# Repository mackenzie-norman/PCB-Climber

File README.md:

# PCB Climber 
Mackenzie Norman

This started as my attempt to implement the GA described in this [paper](https://asmedigitalcollection.asme.org/electronicpackaging/article-abstract/118/1/11/404553/PCB-Layout-Design-Using-a-Genetic-Algorithm?redirectedFrom=fulltext) using the Rust Programming language 

Note: since it is paywalled, and to make sure I knew what I was doing. I rewrote the key pieces here : [GA_breakdown.pdf](GA_breakdown.pdf)

This project uses a Genetic Algorithm (GA) to generate "good" pcb layouts. It can read in some .kicad_pcb files. It features a CLI using CLAP and is multithreaded using Rayon. It also uses the plotters library to make nice plots of  placements.

The GA optimizes for 3 variables which are summed to calculate the fitness. 
- HPWL: calculated on a per net basis. In the real world, layouts with Via anywhere don't need to worry about routing gnd so I sometimes ignore it.
- placement area: currently this is just the bounding box of all the components, ideally this should be Convex Hull or some other more accurate area calculation
- Overlap: A large penalty is added if components overlap.

# Building 
to build the exe simply run :
```cargo build --release``` 
the .exe will then be in 
`target\release\pcb-layout.exe`

# Usage 
Now either with the path above, or just with `cargo run --release --` you can run the exe and use the cli. 
```
Usage: pcb-layout.exe [OPTIONS]

Options:
  -f, --file <FILE>
          Name of the .kicad_pcb file to use. Use synthetic to use the generated toy case. This probably will error on some boards. The parser was a bit of an afterthought and desperately needs more time [default: "../arduino_kicad/arduino UNO.kicad_pcb"]
  -g, --generations <GENERATIONS>
          Number of generations [default: 1000]
  -p, --population-size <POPULATION_SIZE>
          How many individuals are in our popuation [default: 100]
  -t, --test
          Run the testing function on our file (will override gen/pop)- right now this is the only way to see SA results too
  -s, --selection
          Selection Type (ev or elitist) 
  -a, --animate
          Generate an animation
      --threads <THREADS>
          Number of threads (GA only), this is a bit of misnomer since its really how many groups the populations will be split into and then rayon deals with it [default: 1]
  -h, --help
          Print help
  -V, --version
          Print version
``` 

# Project Structure 

- [plcmnt.rs](pcb-layout/src/plcmnt.rs)
- [ga.rs](pcb-layout/src/ga.rs)
- [sa.rs](pcb-layout/src/sa.rs)
- [kicad_parse.rs](pcb-layout/src/kicad_parse.rs)
- [main.rs](pcb-layout/src/main.rs)

Main is our runner and cli, plus a helper function for generating a dummy placment if you don't have a kicad_pcb 
GA has our various selection operators and has the struct and impl for our individual. 
Kicad parse is for parsing kicad_pcb files. Its really ugly right now and kind of buggy I think. 
plcmnt has our struct representation of a pcb (basically, it really is just boxes and pins)

I attempted to keep an engineering notebook in [little-notebook.md](little-notebook.md).

Now that I have plotting working, you can see the progress by looking at test-100x1000.png and [test.md](pcb-layout/test.md)

# Project Write-up
## How I feel
I think this project exactly met my expectations. I still wish I could've done more. 

The hard part about stuff like this is juggling between learning and results, and I think as usual I prioritized "results" over learning and kind of wish it would've been different. 10 week terms are hard. A good example is parallelism and the rand functions. I never really got any speed ups from running things in parallel either with threads or Rayon. I assume part of this is me using clone to heavily since I did not want to deal with references and part of this is my rand function. (also maybe this isnt a great parallel problem). 

## Wins
- Did implement all my GA functionality
- Implemented an SA too and even started on a PSA. 
- Can parse a pcb (sort of)
- At least added parallel computing (using both rayon and std::threads)

## Not Wins
- Ended up giving up on the discretized version of the code - I might return to this later since I still want to do it. The main reason why this was neccessary is that most pcbs don't use whole numbers and so you'd have to scale things up and round. 
- As mentioned above, parallel did not result in meaningful run time improvement
- Using a lot of clones still. Not too expensive but there certainly can be some improvements.
- It seems like I broke it in one of the newer versions. It still runs but we get some overlaps which ideally would be filtered out
- Ran out of time to do any serious testing

## Continuations
I do plan on keeping up with this project, if nothing else to improve my rust skills. This is what I hope to change/add (in no particular order)
- finish PSA , I really think this is the best hill climber ND approach to this problem.
- Try a more 'annealing' based approach to SA. i.e instead of using purely random movement, weighting our movement and swap ops so that when temperature decreases - odds of big movements/ swaps decrease. 
- Try to get a more accurate wirelength calc - this might be something that parallel can help with.  
- Maybe try a marco or some sort of expression parser for dealing with kicad files. (I really wish the kicad parse crate had worked. )
- output back to the kicad_file

## PCB Sources:
[https://github.com/sabogalc/KiCad-Arduino-Boards](https://github.com/sabogalc/KiCad-Arduino-Boards)
## Previous Work/Sources

- [https://docs.rs/kicad_parse_gen/latest/kicad_parse_gen/layout/index.html](https://docs.rs/kicad_parse_gen/latest/kicad_parse_gen/layout/index.html)
- [https://github.com/racklet/kicad-rs/tree/main](https://github.com/racklet/kicad-rs/tree/main)
- [https://github.com/The-OpenROAD-Project/SA-PCB](https://github.com/The-OpenROAD-Project/SA-PCB)
- [https://dspace.mit.edu/bitstream/handle/1721.1/139247/Crocker-pcrocker-meng-eecs-2021-thesis.pdf?sequence=1&isAllowed=y ](https://dspace.mit.edu/bitstream/handle/1721.1/139247/Crocker-pcrocker-meng-eecs-2021-thesis.pdf?sequence=1&isAllowed=y)
- [https://ieeexplore.ieee.org/stamp/stamp.jsp?tp=&arnumber=6269973](https://ieeexplore.ieee.org/stamp/stamp.jsp?tp=&arnumber=6269973)

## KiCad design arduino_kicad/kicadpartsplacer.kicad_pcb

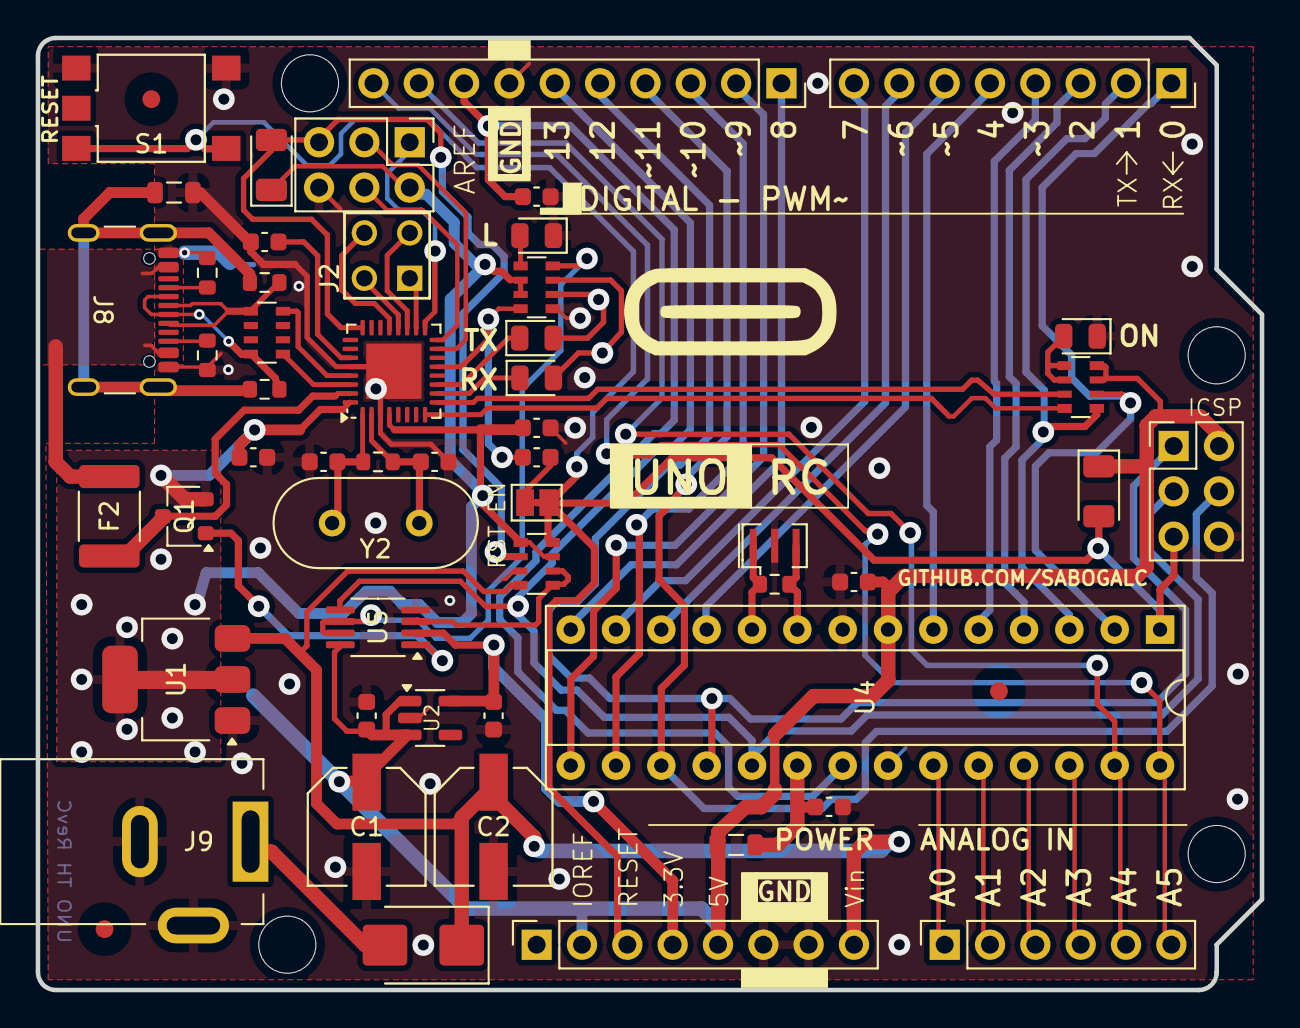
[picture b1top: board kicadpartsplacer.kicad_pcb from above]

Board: 2 copper layers, 68.6 x 53.3 mm, 56 parts (1 on the bottom side), 62 nets.

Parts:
C1, C2: 47u; CAP_EEHZA1E470P
C3, C4, C6, C7, C8, C9, C12: 100n; C_0603_1608Metric
C5, C10: 1u; C_0603_1608Metric
C11, C13: 22p; C_0603_1608Metric
D1: CGRB307-G; D_SMB
D2, D3: CD1206-S01575; D_1206_3216Metric
D4, D5, D6: YELLOW; LED_0805_2012Metric
D7: GREEN; LED_0805_2012Metric
F2: MF-MSMF050-2; Fuse_1812_4532Metric_Pad1.30x3.40mm_HandSolder
FB1: 1kΩ@100MHz; L_0805_2012Metric
FB2: 10uH; L_0805_2012Metric
FID1, FID2, FID3: Fiducial; Fiducial_1mm_Mask3mm
J1, J3: M20-9980345; PinHeader_2x03_P2.54mm_Vertical
J2: M20-9980245; CONN_M20-9980245_HRW
J4: PPTC101LFBN-RC; PinSocket_1x10_P2.54mm_Vertical
J5, J7: PPTC081LFBN-RC; PinSocket_1x08_P2.54mm_Vertical
J6: PPTC061LFBN-RC; PinSocket_1x06_P2.54mm_Vertical
J8: USB_C_Receptacle_USB2.0_16P; USB_C_Receptacle_GCT_USB4105-xx-A_16P_TopMnt_Horizontal
J9: PJ-102AH; BarrelJack_Kycon_KLDX-0202-xC_Horizontal
JP1, JP2: SolderJumper_2_Open; SolderJumper-2_P1.3mm_Open_Pad1.0x1.5mm
Q1: FDN340P; SC-59
R1, R2: 1M; R_0603_1608Metric
R3, R4: 5k1; R_0603_1608Metric
RN1: 10k; R_Array_Convex_4x0603
RN2, RN4: 1k; R_Array_Convex_4x0603
RN3: 22R; R_Array_Convex_4x0603
S1: TS06-667-30-BK-100-G-SMT-TR; SW_TS06-667-30-BK-100-G-SMT-TR
U1: NCP1117-5.0_SOT223; SOT-223-3_TabPin2
U2: LP2985-3.3; SOT-23-5
U3: ATMEGA16U2-MU; VQFN-32-1EP_5x5mm_P0.5mm_EP3.1x3.1mm
U4: ATMEGA328P-PU; DIP-28_W7.62mm_Socket
U5: LMV358IDGKR; MSOP-8_3x3mm_P0.65mm
Y1: CSTNE16M0V530000R0; Resonator_SMD_Murata_CSTxExxV-3Pin_3.0x1.1mm
Y2: LFXTAL003240BULK; Crystal_HC49-4H_Vertical
Z1, Z2: 5pF@1MHz; R_0603_1608Metric

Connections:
+3.3V: C5.2, J7.4, U2.5 (VOUT), U5.2
+5V: C1.1, C3.2, C4.1, C8.2, C9.1, D2.1 (K), D3.1 (K), FB2.1, J1.2, J3.2, J7.2, J7.5, Q1.2 (S), RN1.3 (R3.1), RN1.5 (R4.2), RN2.2 (R2.1), RN2.3 (R3.1), RN4.3 (R3.1), RN4.4 (R4.1), U1.2 (VO), U2.1 (VIN), U2.3 (ON/~OFF), U3.4 (VCC), U3.32 (AVCC), U4.7 (VCC), U5.8 (VCC+)
AD0: J6.1, U4.23 (PC0)
AD1: J6.2, U4.24 (PC1)
AD2: J6.3, U4.25 (PC2)
AD3: J6.4, U4.26 (PC3)
AD4/SDA: J4.9, J6.5, U4.27 (PC4)
AD5/SCL: J4.10, J6.6, U4.28 (PC5)
AREF: C6.1, J4.8, U4.21 (AREF)
AVCC: C12.1, FB2.2, U4.20 (AVCC)
CC1: J8.A5 (CC1), R3.1
CC2: J8.B5 (CC2), R4.1
CMP: RN1.1 (R1.1), RN1.2 (R2.1), U5.3
D+: J8.A6 (D+), J8.B6 (D+), RN3.5 (R4.2), Z1.1
D-: J8.A7 (D-), J8.B7 (D-), RN3.8 (R1.2), Z2.1
DTR: C7.1, RN2.4 (R4.1), U3.13 (PD7)
GATE_CMD: Q1.1 (G), U5.1
GND: C1.2, C2.2, C3.1, C4.2, C5.1, C6.2, C8.1, C9.2, C10.1, C11.2, C12.2, C13.2, D4.1 (K), D7.1 (K), FB1.2, J1.6, J3.6, J4.7, J7.6, J7.7, J8.A1 (GND), J8.A12 (GND), J8.B1 (GND), J8.B12 (GND), J9.2, J9.3, JP2.1 (A), JP2.2 (B), R3.2, R4.2, RN1.7 (R2.2), RN2.5 (R4.2), S1.1, S1.2, U1.1 (GND), U2.2 (GND), U3.3 (GND), U3.28 (UGND), U3.33 (EXP), U4.8 (GND), U4.22 (GND__1), U5.4 (GND), Y1.2
IO0: J5.1, RN4.2 (R2.1), U4.2 (PD0)
IO1: J5.2, RN4.1 (R1.1), U4.3 (PD1)
IO2: J5.3, U4.4 (PD2)
IO3: J5.4, U4.5 (PD3)
IO4: J5.5, U4.6 (PD4)
IO5: J5.6, U4.11 (PD5)
IO6: J5.7, U4.12 (PD6)
IO7: J5.8, U4.13 (PD7)
IO8: J4.1, U4.14 (PB0)
IO9: J4.2, U4.15 (PB1)
M8RXD: RN4.7 (R2.2), U3.9 (PD3)
M8TXD: RN4.8 (R1.2), U3.8 (PD2)
MISO: J3.1, J4.5, U4.18 (PB4)
MISO2: J1.1, U3.17 (PB3)
MOSI: J3.4, J4.4, U4.17 (PB3)
MOSI2: J1.4, U3.16 (PB2)
unnamed: D1.2 (A), J9.1
unnamed: D4.2 (A), RN2.1 (R1.1)
unnamed: D5.2 (A), RN2.6 (R3.2)
unnamed: D6.2 (A), RN2.7 (R2.2)
unnamed: D7.2 (A), RN4.5 (R4.2), RN4.6 (R3.2)
unnamed: RN2.8 (R1.2), U5.6, U5.7
unnamed: C13.1, R1.1, U3.2 (PC0), Y2.1
unnamed: C10.2, U3.27 (UCAP)
unnamed: C11.1, R1.2, U3.1 (XTAL1), Y2.2
unnamed: R2.2, U4.9 (PB6), Y1.3
unnamed: R2.1, U4.10 (PB7), Y1.1
PB4: J2.1, U3.18 (PB4)
PB5: J2.3, U3.19 (PB5)
PB6: J2.2, U3.20 (PB6)
PB7: J2.4, U3.21 (PB7)
RD+: RN3.4 (R4.1), U3.29 (D+)
RD-: RN3.1 (R1.1), U3.30 (D-)
RESET: C7.2, D2.2 (A), J3.5, J7.3, JP1.1 (A), JP1.2 (B), RN1.4 (R4.1), S1.3, S1.4, U4.1 (PC6/~RESET)
RESET2: D3.2 (A), J1.5, RN1.6 (R3.2), U3.24 (PC1//~RESET)
RXLED: D6.1 (K), U3.10 (PD4)
SCK: J3.3, J4.6, U4.19 (PB5), U5.5
SCK2: J1.3, U3.15 (PB1)
SS: J4.3, U4.16 (PB2)
TXLED: D5.1 (K), U3.11 (PD5)
USBVCC: F2.2, Q1.3 (D), U3.31 (UVCC)
USHIELD: FB1.1, J8.S1 (SHIELD), Z1.2, Z2.2
VCC: C2.1, D1.1 (K), J7.8, RN1.8 (R1.2), U1.3 (VI)
XUSB: F2.1, J8.A4 (VBUS), J8.A9 (VBUS), J8.B4 (VBUS), J8.B9 (VBUS)

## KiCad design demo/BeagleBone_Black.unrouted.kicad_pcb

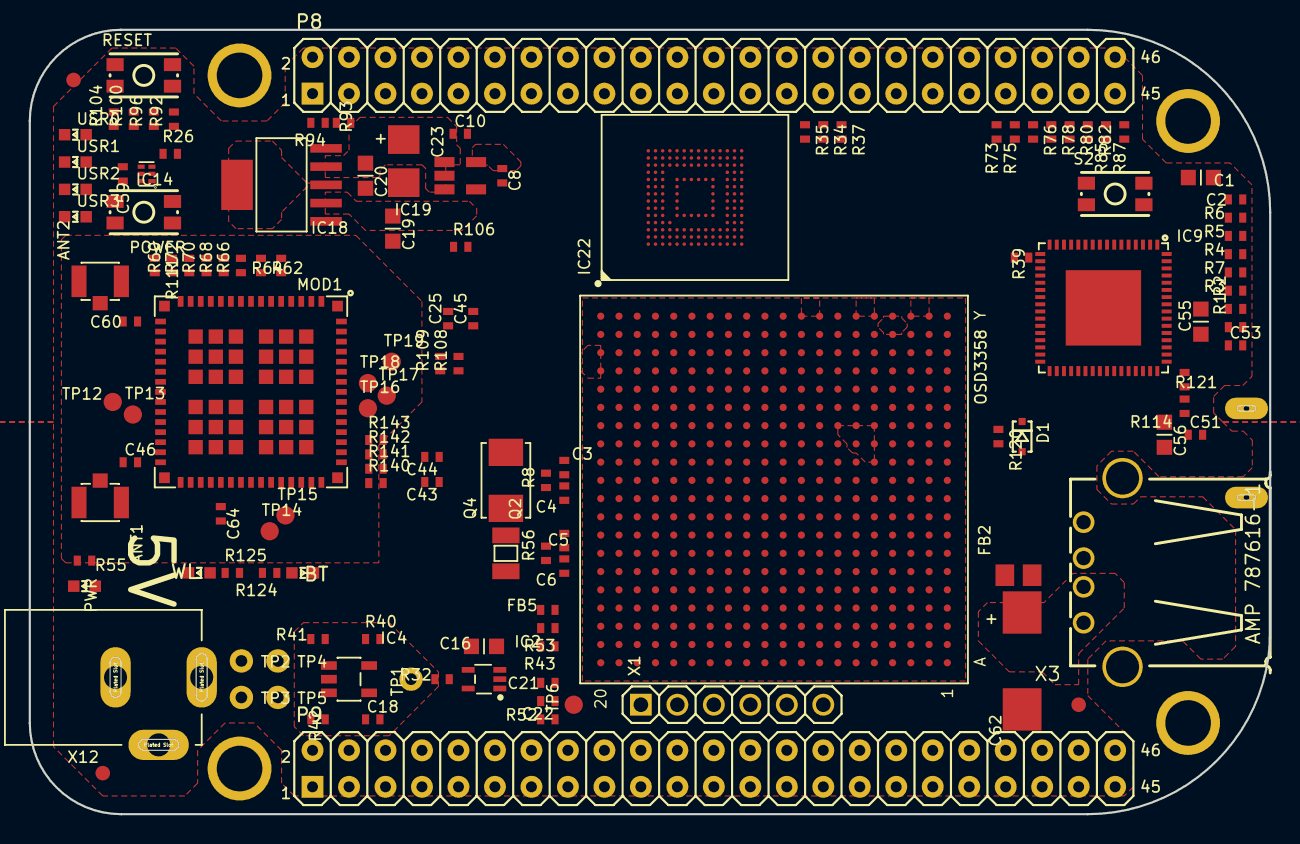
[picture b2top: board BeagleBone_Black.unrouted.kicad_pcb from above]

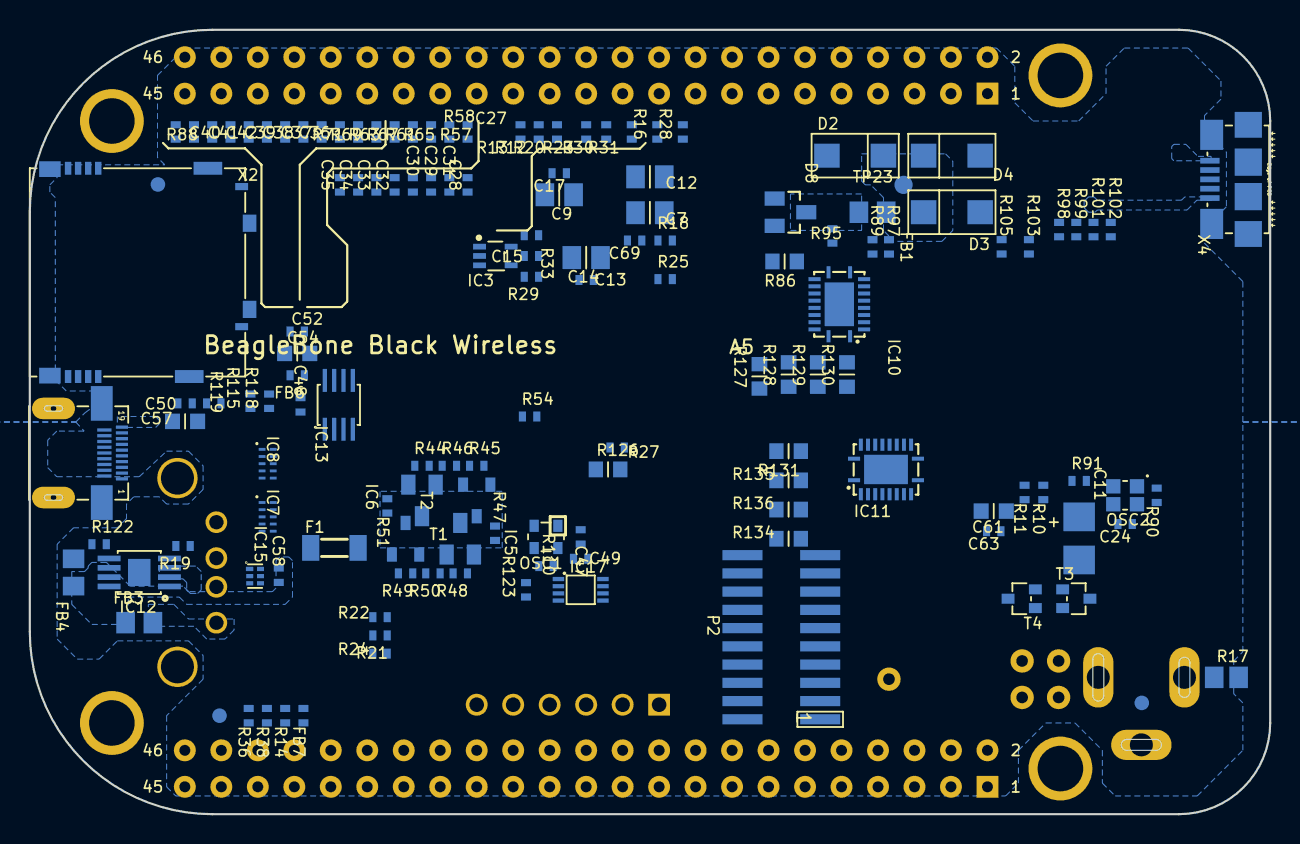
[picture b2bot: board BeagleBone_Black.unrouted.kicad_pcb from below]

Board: 6 copper layers, 86.4 x 54.6 mm, 275 parts (139 on the bottom side), 262 nets, no tracks yet.

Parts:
ANT1, ANT2: U.FL-R-SMT-1(10); U.FL-R-SMT-1
BT: LTST-C191TBKT; 0603-LED
C1: 10uF,10V; C0603K
C2, C13, C15, C17, C18, C21, C22, C24, C25, C43, C44, C45, C47, C48, C49, C50, C51, C52, C53, C58, C59, C63, C69: .1uF, 6.3V; C0402K
C3, C4, C5, C6: 18pF, 50V; C0402K
C7: 4.7uF, 6.3V; C0805K
C8, C10: 1uF; C0402K
C9, C12, C14: 2.2uF, 6.3V; C0805K
C11, C23: 47uF DNP; CT3528
C16, C54, C55, C56, C57: 2.2uF, 6.3V; C0603K
C19, C20, C61: 10uF, 6.3V; C0603K
C27, C28, C29, C30, C31, C32, C33, C34, C35, C36, C37, C38, C39, C40, C41, C42: 47pF, 6.3V; C0402K
C46, C60: 10pF; C0402K
C62: 220uF 6.3V; D_7343-31W
C64: 1uF, 6.3V; C0402K
D1: RB751V40,115; SOD323(NXP)REFLOW
D2: STPS140A DNP; DIODE_SMA
D3, D4: STPS140A; DIODE_SMA
D8: BAT54C; SOT23
F1: 1206L025YR; SM-1206
FB1: 220 Ohm 800mA; 0805-RESISTOR
FB2: 2.5k Ohm (BLM18BD252SN1D); 0805-RESISTOR
FB3: 150 Ohm 800mA; 0805-RESISTOR
FB4: 0.1 Ohm, 0805; 0805-RESISTOR
FB5, FB6, FB7: 1k BLM15AG102SN1D; R0402
FUD1, FUD2, FUD3, FUD4, FUD5, FUD6: FIDUCIAL; FIDUCIAL_40MIL
IC1: OSD3358
IC2: SN74LVC1G07DCK; SC70(TI-DCK)
IC3: SN74LVC1G06DCK; SC70(TI-DCK)
IC4: 24LC32AT-I/OT; SOT23-5(MICROCHIP)
IC5: TLVH431 (SOT-23-3); DBZ_R-PDSO-G3
IC6: DNP TLVH431 (SOT-23-3); DBZ_R-PDSO-G3
IC7, IC8: IP4283CZ10-TBR; SOT1176-1(NXP)
IC9: TDA19988BHN/C1,557; SOT804-4(NXP)
IC10, IC11: TXS0108ERGYR; R-PVQFN-N20(TI)
IC12: TPS2051BDGN; MSOP-POWER.PAD-8(TI)
IC13: SN74AUC1G74; SM8-8(TI)
IC14, IC15: TPD4S012DRY; SON-6(TI)-DRY
IC17: SN74LVC2G241DCUR; VSSOP8(TI)
IC18: TL1963ADCQR; SOT-223(DCQ_R-PDSO-G6_TI)
IC19: AP2112K-1.8TRG1 3.3V; SOT23-5
IC22: MICRON_EMMC_153
MGT1, MGT2, MGT3, MGT4: MOUNTING_HOLE
MOD1: WL1835MODGBMOCT; MOC-100(TI)
OSC1: ASDMB-24.576MHZ-LC-T; OSCILLATOR-2.5X2.0-BBB
OSC2: NZ2520SB-32.768KHZ-NSA3534C; NZ2520S
P2: JTAG
P8, P9: TH-2X23
POWER: MINI_PUSHBUTTON
PWR: LTST-C191TBKT; 0603-LED
Q2: 32.768kHz; CRYSTAL_3.2X1.5
Q4: 24 MHz; CRYSTAL_5X3.2MM
R1, R2, R3, R4, R5, R6, R7, R12, R13, R16, R18, R19, R20, R23, R24, R25, R28, R30, R31, R32, R33, R40, R119, R121: 10k, 1%; R0402
R8: 1M, 1%; R0402
R10, R11: 150k; R0402
R14, R26, R27, R29, R35, R36, R37, R38, R39, R54, R114, R122: 0, 1%; R0402
R17: .1, 0805; R0805
R21, R22, R43, R52, R53, R55: 4.75k, 1%; R0402
R34: 22; R0402
R41, R42, R115, R118: 1.5k, 1%; R0402
R44: 499; R0402
R45, R49: DNP; R0402
R46: 10k 1%; R0402
R47: 40.2k 1%; R0402
R48: DNP 499; R0402
R50: DNP 10k 1%; R0402
R51: DNP 40.2k 1%; R0402
R56: DNP 1M, 1%; R0402
R57, R58, R61, R63, R65, R67, R69, R71, R73, R75, R76, R78, R80, R82, R85, R87, R123: 100k, 1%; R0402
R60, R62, R64, R66, R68, R70, R72, R140, R141, R142, R143: 33, 5%; R0402
R86, R126, R127, R128, R129, R130, R131, R134, R135, R136: 33, 5%; R0603
R88: 100, 1%; R0402
R89, R90, R92, R96, R100, R104, R124, R125: 1k; R0402
R91: 0 DNP; R0402
R93: 7.15k; R0402
R94: 4.12k; R0402
R95: 1M; R0402
R97, R108, R109: DNP 1k; R0402
R98, R99, R101, R102, R103, R105: 10k; R0402
R106: 1.5k; R0402
R110: 33; R0402
R111: DNP 10k; R0402
R120: 27k, 1%; R0402
RESET: MINI_PUSHBUTTON
S2: MINI_PUSHBUTTON
T1: MMBT2907; SOT23-BEC
T2: DNP MMBT2907; SOT23-BEC
T3, T4: BSS138W-7-F; SOT-323(DIODES)
TP1, TP2, TP3, TP4, TP5: TESTPAD/W_HOLE_1X1; TESTPAD_W_HOLE_1X1
TP6, TP12, TP13, TP14, TP15, TP16, TP17, TP18, TP19, TP23: PTR1B1,27; B1,27
USR0, USR1, USR2, USR3: LTST-C191TBKT; 0603-LED
WL: LTST-C191TBKT; 0603-LED
X1: TH-1X6
X2: SCHA5B0200
X3: USB_HOST_HORIZONTAL_W_CHASSIS_GND
X4: 10118192-0001LF; 10118192-0001LF(MICRO-USB-B-AMPHENOL-FCI)
X5: 10118241-001RLF; HDMI-TYPE-D-10118241
X12: PJ-102B_POWER_CON

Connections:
3.3V-WIFI: C8.1, C11.+, C24.1, C25.1, C43.1, C64.1, IC10.2, IC11.2, IC19.5, MOD1.38, OSC2.4, R90.1, R98.1, R99.1, R101.1, R102.1, R103.1, R105.1, R111.1
5V_IN: C19.1, D8.3, FB1.2, IC18.2, R95.1
12MHZ: FB6.2, IC9.27
12M_LOOP: IC13.2, IC13.3
32.768KHZ: MOD1.36, OSC2.3, R91.2
AGND: IC1.A6, IC1.A9, IC1.E8, P9.34
AIN0: IC1.B6, P9.39
AIN1: IC1.C7, P9.40
AIN2: IC1.B7, P9.37
AIN3: IC1.A7, P9.38
AIN4: IC1.C8, P9.33
AIN5: IC1.B8, P9.36
AIN6: IC1.A8, P9.35
AIN7: IC1.C9, R21.2, R22.1
ALT.BT.EN: IC10.10, IC11.10, R106.1, R131.1
ALT.BUFF.OE: IC10.15, R126.2
ALT.WL.CLK: IC11.18, R136.2
ALT.WL.CMD: IC11.17, R135.2
ALT.WL.D0: IC10.18, R129.2
ALT.WL.D1: IC10.17, R128.2
ALT.WL.D2: IC10.16, R127.2
ALT.WL.D3: C10.1, C20.1, C23.+, C44.1, C45.1, C61.1, C63.1, IC10.19, IC11.19, IC18.4, IC19.1, IC19.3, MOD1.46, MOD1.47, R93.1, R124.2, R125.2
ALT.WL.EN: IC11.12, R134.2
ALT.WL.IRQ: IC10.20, R130.2
BAT_TEMP: IC1.W1, TP4.P$1
BAT_VOLT: IC1.Y1, TP3.P$1
BT_EN: IC11.4, MOD1.41, R11.1, T4.G
BT_EN.SIP: IC1.K17, R135.1
BT_HCI_CTS: IC11.8, R141.2
BT_HCI_CTS.SIP: IC1.M17, IC11.15, R108.1
BT_HCI_RTS: IC11.6, R140.2
BT_HCI_RTS.SIP: IC1.M18, IC11.13, R109.1
BT_HCI_RX: IC11.1, R143.2
BT_HCI_RX.SIP: IC1.L17, IC11.14
BT_HCI_TX: IC11.7, R142.2
BT_HCI_TX.SIP: IC1.L16, IC11.20
CEC: D1.C, IC9.30, X5.15
CGND: T3.D, WL.K
CLKOUT2: FB7.1, IC11.16, P2.18, P9.41, R14.1
DVI_5V: F1.1, R115.1, R118.1, X5.19
EHRPWM1A: IC1.U14, P9.14
EHRPWM1B: IC1.T14, P9.16
EHRPWM2A: IC1.U10, P8.19
EHRPWM2B: IC1.T10, P8.13
EMMC_RSTN: IC22.K5, R29.1, R33.1
EXT_SWING: IC9.34, R119.1
GND: ANT1.GND1, ANT1.GND2, ANT2.GND1, ANT2.GND2, C1.2, C2.2, C7.2, C8.2, C9.2, C10.2, C11.-, C12.2, C13.2, C14.2, C15.2, C16.2, C17.2, C18.2, C19.2, C20.2, C21.2, C22.2, C23.-, C24.2, C25.2, C27.2, C28.2, C29.2, C30.2, C31.2, C32.2, C33.2, C34.2, C35.2, C36.2, C37.2, C38.2, C39.2, C40.2, C41.2, C42.2, C43.2, C44.2, C45.2, C47.2, C48.2, C49.2, C50.2, C51.2, C52.2, C53.2, C54.2, C55.2, C56.2, C57.2, C58.2, C59.2, C61.2, C62.-, C63.2, C64.2, C69.2, D8.2, IC1.A1, IC1.A18, IC1.E19, IC1.E20, IC1.F8, IC1.F19, IC1.G8, IC1.G9, IC1.G11, IC1.G12, IC1.G19, IC1.H6, IC1.H7, IC1.H8, IC1.H9, IC1.H10, IC1.H12, IC1.H19, IC1.J6, IC1.J7, IC1.J8, IC1.J9, IC1.J10, IC1.J11, IC1.J19, IC1.J20, IC1.K7, IC1.K9, IC1.K10, IC1.K11, IC1.K19, IC1.L10, IC1.L11, IC1.L12, IC1.L13, IC1.L19, IC1.M6, IC1.M7, IC1.M8, IC1.M9, IC1.M10, IC1.M12, IC1.M14, IC1.M19, IC1.N7, IC1.N10, IC1.N11, IC1.N14, IC1.N19, IC1.N20, IC1.P19, IC1.P20, IC1.R19, IC1.R20, IC1.T19, IC1.T20, IC1.U19, IC1.V1, IC1.V18, IC1.V19, IC1.W2, IC1.W3, IC1.W5, IC1.W6, IC1.W7, IC1.W8, IC1.W9, IC1.W10, IC1.W11, IC1.W12, IC1.W13, IC1.W14, IC1.W15, IC1.W16, IC1.W17, IC1.W18, IC1.W19, IC1.W20, IC1.Y7, IC1.Y10, IC1.Y12, IC1.Y15, IC1.Y18, IC2.3, IC3.3, IC4.2, IC7.3, IC7.8, IC8.3, IC8.8, IC9.8, IC9.9, IC9.16, IC9.17, IC9.18, IC9.19, IC9.53, IC9.54, IC9.61, IC9.62, IC9.63, IC9.65, IC10.11, IC10.TP, IC11.11, IC11.TP, IC12.1, IC12.9, IC13.4, IC14.4, IC15.4, IC17.1, IC17.4, IC18.3, IC18.6, IC19.2, IC22.C4, IC22.E7, IC22.G5, IC22.H10, IC22.K8, IC22.N2, IC22.N5, IC22.P4, IC22.P6, MOD1.1, MOD1.7, MOD1.9, MOD1.15, MOD1.16, MOD1.17, MOD1.19, MOD1.20, MOD1.23, MOD1.24, MOD1.28, MOD1.29, MOD1.30, MOD1.31, MOD1.33, MOD1.34, MOD1.35, MOD1.37, MOD1.39, MOD1.44, MOD1.45, MOD1.48, MOD1.49, MOD1.54, MOD1.55, MOD1.59, MOD1.61, MOD1.63, MOD1.64, MOD1.G1, MOD1.G2, MOD1.G3, MOD1.G4, MOD1.G5, MOD1.G6, MOD1.G7, MOD1.G8, MOD1.G9, MOD1.G10, MOD1.G11, MOD1.G12, MOD1.G13, MOD1.G14, MOD1.G15, MOD1.G16, MOD1.G17, MOD1.G18, MOD1.G19, MOD1.G20, MOD1.G21, MOD1.G22, MOD1.G23, MOD1.G24, MOD1.G25, MOD1.G26, MOD1.G27, MOD1.G28, MOD1.G29, MOD1.G30, MOD1.G31, MOD1.G32, MOD1.G33, MOD1.G34, MOD1.G35, MOD1.G36, OSC1.2, OSC2.2, P2.4, P2.8, P2.10, P2.12, P2.16, P2.20, P8.1, P8.2, P9.1, P9.2, P9.43, P9.44, P9.45, P9.46, POWER.1, POWER.2, R10.2, R11.2, R17.1, R19.2, R22.2, R24.1, R27.2, R52.2, R55.1, R57.1, R61.1, R63.1, R65.1, R67.1, R69.1, R71.1, R73.1, R75.1, R85.1, R87.1, R94.2, R95.2, R106.2, R108.2, R109.2, R114.1, R119.2, R123.2, RESET.1, RESET.2, S2.3, S2.4, T3.S, T4.S, TP5.P$1, USR0.K, USR1.K, USR2.K, USR3.K, X1.1, X2.6, X2.GND, X3.4, X4.GND, X5.4, X5.7, X5.10, X5.13, X5.16, X12.OUT
GPIO0_7: P9.42, R36.1, R38.1
GPIO0_26: IC1.T11, P8.14
GPIO0_27: IC1.U12, P8.17
GPIO1_12: IC1.T12, P8.12
GPIO1_13: IC1.R12, P8.11
GPIO1_14: IC1.V13, P8.16
GPIO1_15: IC1.U13, P8.15
GPIO1_16: P9.15, R54.1
GPIO1_16.SIP: IC1.R13, R54.2
GPIO1_17: IC1.V14, P9.23
GPIO1_28: IC1.U18, P9.12
GPIO1_29: IC1.V6, P8.26
GPIO2_1: IC1.V12, P8.18
GPIO3_19: IC1.C13, P9.27
GPIO3_21: IC1.A14, P9.25, R110.2
HDMI.DSCL: IC9.33, R115.2, X5.17
HDMI.DSDA: IC9.32, R118.2, X5.18
HDMICLK_DIS#: IC1.V17, OSC1.1
HDMI_1V8: C50.1, C51.1, C52.1, C53.1, C54.1, C55.1, C56.1, C57.1, FB2.2, IC9.5, IC9.14, IC9.29, IC9.35, IC9.36, IC9.41, IC9.46, IC9.47, IC9.48, IC9.55
HDMI_INT: IC1.U16, IC9.50, R121.2
HPD: IC9.31, X5.1
I2C0_SCL: IC1.C16, IC1.C20, IC4.1, IC9.52, R41.2
I2C0_SDA: IC1.C17, IC1.C19, IC4.3, IC9.51, R42.2
I2C1_SCL: IC1.A16, P9.17
I2C1_SDA: IC1.B16, P9.18
I2C2_SCL: IC1.D17, P9.19
I2C2_SDA: IC1.D18, P9.20
JTAG_EMU0: IC1.C14, P2.13, R43.2
JTAG_EMU1: IC1.B14, P2.14, R53.2
JTAG_TCK: IC1.A12, P2.9, P2.11
JTAG_TDI: IC1.B11, P2.3
JTAG_TDO: IC1.A11, P2.7
JTAG_TMS: IC1.C11, P2.1
JTAG_TRSTN: IC1.B10, P2.2, R52.1
LCD.CLOCK: IC9.4, P8.28, R34.1
LCD.D0.B0--B3: C42.1, IC1.R1, IC9.15, P8.45, R87.2
LCD.D1.B1--B4: C41.1, IC1.R2, IC9.13, P8.46, R85.2
LCD.D2.B2--B5: C40.1, IC1.R3, IC9.12, P8.43, R82.1, R88.1
LCD.D3.B3--B6: C39.1, IC1.R4, IC9.11, P8.44, R80.1
LCD.D4.B4--B7: C38.1, IC1.T1, IC9.10, P8.41, R78.1
LCD.D5.G0--G2: C37.1, IC1.T2, IC9.7, P8.42, R76.1
LCD.D6.G1--G3: C36.1, IC1.T3, IC9.6, P8.39, R75.2
LCD.D7.G2--G4: C35.1, IC1.T4, IC9.3, P8.40, R73.2
LCD.D8.G3--G5: C34.1, IC1.U1, IC9.2, P8.37, R71.2
LCD.D9.G4--G6: C33.1, IC1.U2, IC9.1, P8.38, R69.2
LCD.D10.G5--G7: C32.1, IC1.U3, IC9.64, P8.36, R67.2
LCD.D11.R0--R3: C31.1, IC1.U4, IC9.60, P8.34, R65.2
LCD.D12.R1--R4: C30.1, IC1.V2, IC9.59, P8.35, R63.2
LCD.D13.R2--R5: C29.1, IC1.V3, IC9.58, P8.33, R61.2
LCD.D14.R3--R6: C28.1, IC1.V4, IC9.57, P8.31, R58.1
LCD.D15.R4--R7: C27.1, IC1.T5, IC9.56, P8.32, R57.2
LCD.ENABLE: IC9.20, P8.30, R39.1
LCD.HSYNC: IC9.22, P8.29, R37.1
LCD.VSYNC: IC9.21, P8.27, R35.1
LDO_PGOOD: IC1.B5, IC1.B20
LS_BUF_OE: IC1.L18, R131.2
MCU.LCD.CLK: IC1.V5, R34.2
MCU.LCD.EN: IC1.R6, R39.2
MCU.LCD.HS: IC1.R5, R37.2
MCU.LCD.VS: IC1.U5, R35.2
MMC1_CLK: IC1.U9, IC22.M6, P8.21, R31.1
MMC1_CMD: IC1.V9, IC22.M5, P8.20, R30.1
MMC1_DAT0: IC1.U7, IC22.A3, P8.25, R12.1
MMC1_DAT1: IC1.V7, IC22.A4, P8.24, R13.1
MMC1_DAT2: IC1.R8, IC22.A5, P8.5, R16.1
MMC1_DAT3: IC1.T8, IC22.B2, P8.6, R18.1
MMC1_DAT4: IC1.U8, IC22.B3, P8.23, R20.1
MMC1_DAT5: IC1.V8, IC22.B4, P8.22, R23.1
MMC1_DAT6: IC1.R9, IC22.B5, P8.3, R25.1
MMC1_DAT7: IC1.T9, IC22.B6, P8.4, R28.1
unnamed: OSC2.1, R90.2
unnamed: R88.2, S2.1, S2.2
unnamed: FB5.1, IC1.A15
unnamed: PWR.K, R55.2
unnamed: IC18.1, R89.2, R97.2
unnamed: C4.1, IC1.K20, Q4.1, R8.1
unnamed: C3.1, IC1.M20, Q4.2, R8.2
unnamed: IC1.C6, IC1.D19
unnamed: IC18.5, R93.2, R94.1
unnamed: C3.2, C4.2, IC1.L20
unnamed: C5.2, C6.2, IC1.G20
unnamed: ANT2.SIG, C60.1
unnamed: ANT1.SIG, C46.1
unnamed: C46.2, MOD1.32
unnamed: R100.1, USR1.A
unnamed: R96.1, USR2.A
unnamed: R92.1, USR3.A
unnamed: C60.2, MOD1.18
unnamed: IC1.P17, R27.1
unnamed: IC1.B4, R24.2
unnamed: BT.K, T4.D
unnamed: R125.1, WL.A
unnamed: IC1.D13, R14.2
unnamed: FB7.2, IC1.D14
unnamed: IC1.R14, IC3.2
unnamed: IC3.4, R29.2
unnamed: MOD1.26, TP12.TP
unnamed: R104.1, USR0.A
unnamed: MOD1.27, TP13.TP
unnamed: C5.1, IC1.H20, Q2.P$1, R56.2
unnamed: C6.1, IC1.F20, Q2.P$2, R56.1
unnamed: MOD1.42, TP14.TP
unnamed: MOD1.43, TP15.TP
unnamed: MOD1.56, TP16.TP
unnamed: MOD1.57, TP17.TP
unnamed: OSC1.3, R110.1
unnamed: MOD1.58, TP18.TP
unnamed: MOD1.60, TP19.TP
unnamed: IC1.P15, R26.1
unnamed: C7.1, C69.1, IC22.C2
unnamed: IC1.C18, R36.2
unnamed: IC1.B12, R38.2
unnamed: IC5.2, R44.2, R45.1, T1.B
unnamed: IC5.1, R45.2, R46.2, R47.1
unnamed: IC6.2, R48.2, R49.1, T2.B
unnamed: IC6.1, R49.2, R50.2, R51.1
unnamed: IC4.5, R40.2, TP1.P$1
unnamed: BT.A, R124.1
unnamed: FB6.1, IC13.5
unnamed: MGT1.P$1, MGT2.P$1, MGT3.P$1, MGT4.P$1, R17.2, X2.CGND1, X2.CGND2, X2.CGND3, X2.CGND4, X2.CGND5, X2.CGND6, X3.5, X3.6, X4.CGND1, X4.CGND2, X4.CGND3, X4.CGND4, X4.CGND5, X4.CGND6, X5.CG1, X5.CG2, X5.CG3, X5.CG4
unnamed: MOD1.13, R72.1
unnamed: MOD1.12, R70.1
unnamed: MOD1.11, R68.1
unnamed: MOD1.10, R66.1
unnamed: D1.A, R120.2
unnamed: MOD1.8, R64.1
unnamed: MOD1.6, R62.1
unnamed: MOD1.50, R140.1
unnamed: MOD1.51, R141.1
unnamed: MOD1.52, R142.1
unnamed: MOD1.53, R143.1
unnamed: IC10.14, R86.2
NC3: MOD1.14, R60.1, R111.2
PMIC_INT: IC1.B18, IC1.B19
PMIC_NWAKEUP: IC1.A19, IC1.C5
PMIC_PGOOD: IC1.A20, IC1.B15, IC2.2
PWR_BUT: IC1.D20, P9.9, POWER.3, POWER.4
RX<-TX: IC17.3, X1.5
SD.CD: IC1.C15, P2.19, R7.1, X2.CD
SD.CLK: IC1.G17, R3.1, X2.5
SD.CMD: IC1.G18, R4.1, X2.3
SD.D0: IC1.G16, R2.1, X2.7
SD.D1: IC1.G15, R1.1, X2.8
SD.D2: IC1.F18, R6.1, X2.1
SD.D3: IC1.F17, R5.1, X2.2
SELECT_5V: D2.K, D3.K, D4.K, FB1.1, R97.1, TP23.TP
SLOW_CLK: IC11.5, R91.1
SPI1_CS0: IC1.C12, IC9.25, P9.28
SPI1_D0: IC1.B13, IC9.24, P9.29
SPI1_D1: IC1.D12, P9.30
SPI1_SCLK: IC1.A13, IC9.23, P9.31
SYS_5V: C62.+, D2.A, F1.2, IC1.W4, IC1.Y4, IC12.2, IC12.3, P9.7, P9.8
SYS_RESET#: C16.1, C21.1, IC1.A10, IC2.4, P2.15, P9.10, R32.2, RESET.3, RESET.4
TEST: IC9.49, R114.2
TIMER4: IC1.R7, P8.7
TIMER5: IC1.T6, P8.9
TIMER6: IC1.U6, P8.10
TIMER7: IC1.T7, P8.8
TX0+: IC8.5, IC9.40, X5.9
TX0-: IC8.4, IC9.39, X5.11
TX1+: IC7.2, IC9.43, X5.6
TX1-: IC7.1, IC9.42, X5.8
TX2+: IC7.5, IC9.45, X5.3
TX2-: IC7.4, IC9.44, X5.5
TX->RX: IC17.2, R123.1, X1.4
TXC+: IC8.2, IC9.38, X5.12
TXC-: IC8.1, IC9.37, X5.14
UART0_RST#: IC1.E17, TP6.TP
UART0_RXD: IC1.E15, IC17.6
UART0_TXD: IC1.E16, IC17.5
UART1_RXD: IC1.D16, P9.26
UART1_TXD: IC1.D15, P9.24
UART2_RXD: IC1.A17, P9.22
UART2_TXD: IC1.B17, P9.21
UART4_RXD: IC1.T17, P9.11
UART4_TXD: IC1.U17, P9.13
USB1_DRVVBUS: IC1.F15, IC12.4, R19.1
USB1_OC#: IC1.T16, IC12.5, R122.2
USB1_VBUS: FB4.2, IC1.T18
USB.CLIENT.D+: IC1.N17, IC14.1, X4.D+
USB.CLIENT.D-: IC1.N18, IC14.2, X4.D-
USB.CLIENT.ID: IC1.P16, IC14.3, X4.ID
USB.HOST.D+: IC1.R17, IC15.1, X3.3
USB.HOST.D-: IC1.R18, IC15.2, X3.2
USB_DC: C59.1, D4.A, IC1.Y8, IC1.Y9, IC14.6, R26.2, X4.VBUS
USR0: IC1.V15, R104.2
USR1: IC1.U15, R100.2
USR2: IC1.T15, R96.2
USR3: IC1.V16, R92.2
VBUS.HOST: FB3.2, X3.1
VBUS.OUT: C58.1, FB3.1, FB4.1, IC12.6, IC12.7, IC12.8, IC15.6
VDD_1V8: FB2.1, IC1.D10, IC1.E9, IC1.N16, IC1.R16, IC2.5, IC5.3, IC6.3, R47.2, R51.2, T1.C, T2.C
VDD_3V3A: IC1.N5, IC1.P5, IC1.P6, IC1.P7, R44.1, R46.1, T1.E
VDD_3V3AUX: IC1.Y11, PWR.A
VDD_3V3B: C1.1, C2.1, C9.1, C12.1, C13.1, C14.1, C15.1, C17.1, C18.1, C22.1, C47.1, C48.1, C49.1, IC1.U20, IC1.V20, IC3.5, IC4.4, IC13.6, IC13.7, IC13.8, IC17.7, IC17.8, IC22.C6, IC22.E6, IC22.F5, IC22.J10, IC22.K9, IC22.M4, IC22.N4, IC22.P3, IC22.P5, OSC1.4, P2.5, P9.3, P9.4, R1.2, R2.2, R3.2, R4.2, R5.2, R6.2, R7.2, R12.2, R13.2, R16.2, R18.2, R20.2, R21.1, R23.2, R25.2, R28.2, R30.2, R31.2, R32.1, R33.2, R40.1, R41.1, R42.1, R43.1, R48.1, R50.1, R53.1, R58.2, R76.2, R78.2, R80.2, R82.2, R89.1, R120.1, R121.1, R122.1, T2.E, X2.4
VDD_5V: D3.A, IC1.Y5, IC1.Y6, P9.5, P9.6, X12.IN
VDD_ADC: IC1.A4, IC1.A5, IC1.B9, IC1.D8, P9.32
VIN_BAT: IC1.Y2, IC1.Y3, TP2.P$1
WL_EN: IC11.3, MOD1.40, R10.1, T3.G
WL_EN.SIP: IC1.K18, R136.1
WL_IRQ: IC11.9, R60.2
WL_IRQ.SIP: IC1.H18, R134.1
WL_SDIO_CLK: IC10.6, R64.2, R103.2
WL_SDIO_CLK.SIP: IC1.L15, R126.1
WL_SDIO_CMD: IC10.7, R62.2, R105.2
WL_SDIO_CMD.SIP: IC1.J16, R86.1
WL_SDIO_D0: IC10.1, R66.2, R98.2
WL_SDIO_D0.SIP: IC1.J17, R130.1
WL_SDIO_D1: IC10.3, R68.2, R99.2
WL_SDIO_D1.SIP: IC1.J18, R129.1
WL_SDIO_D2: IC10.4, R70.2, R101.2
WL_SDIO_D2.SIP: IC1.K15, R128.1
WL_SDIO_D3: IC10.5, R72.2, R102.2
WL_SDIO_D3.SIP: IC1.H16, R127.1
XDMA_EVENT_INTRO: FB5.2, IC13.1, P2.17

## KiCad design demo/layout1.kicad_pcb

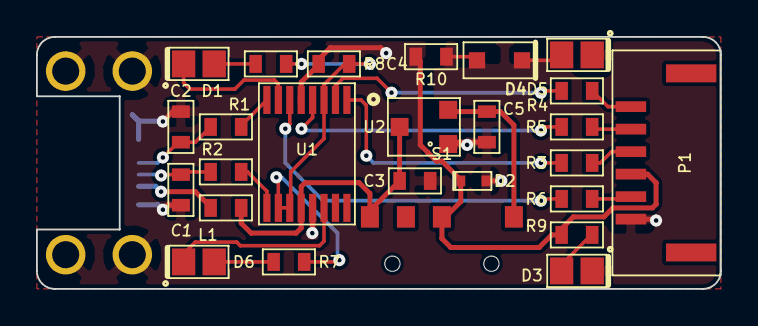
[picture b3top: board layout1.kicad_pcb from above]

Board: 2 copper layers, 38.0 x 14.0 mm, 27 parts (1 on the bottom side), 25 nets.

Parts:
C1, C2: 47pF; 0603_C
C3, C5: 4.7uF; 0603_C
C4: 100nF; 0603_C
D1, D3, D5, D6: LED; 0805_LED
D2: TVS; NXP-PESD-SOD523-SC-79
D4: 3V drop; NXP-SOD323-larger
J1: MICRO-USB-B-alt; USB-MICRO-B-FCI-10103593-0001LF
L1: FB; 0603_L
P1: CONN_01X06; JST-eGH-1.25mm-SMD-top-6
R1, R2, R3, R4, R5, R6: 27; 0603_R
R7, R8, R9, R10: 1k; 0603_R
S1: C_K_AYZ0103AGRLC_SP3T_Switch; C_K_AYZ0103AGRLC-ST3P-Switch
U1: FTDI-FT230X; FTDI-FT230X-SSOP16
U2: MCP1703-alt; SOT-23A_larger_pads

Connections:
+3.3VP: C4.1, R7.2, R8.2, U1.3, U1.10, U1.11
+3V3: C5.1, S1.4, U2.2
+5V: C3.1, L1.2, S1.1, U1.12, U2.3
/D+: C2.1, J1.3, R1.1
/D-: C1.1, J1.2, R2.1
/RXD: R5.1, U1.4
/RXD2: P1.5, R5.2
/TXD: R3.1, U1.1
/TXD2: P1.4, R3.2
/USB+: R1.2, U1.8
/USB-: R2.2, U1.9
/VBUS: J1.1, L1.1
/~CTS2: P1.2, R6.2
/~CTS: R6.1, U1.6
/~RTS2: P1.6, R4.2
/~RTS: R4.1, U1.2
/~RXLED2: D6.1, R7.1
/~RXLED: D6.2, U1.14
/~TXLED2: D1.1, R8.1
/~TXLED: D1.2, U1.7
GND: C1.2, C2.2, C3.2, C4.2, C5.2, D2.1, D3.2, D5.2, J1.5, J1.6, J1.7, J1.8, J1.9, J1.10, J1.11, P1.1, U1.5, U1.13, U2.1
unnamed: D3.1, R9.2
unnamed: D4.1, R10.2
unnamed: D4.2, D5.1
VCC: D2.2, P1.3, R9.1, R10.1, S1.3

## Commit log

2025-01-28 initial_commit
2025-01-28 decide on name I think
2025-01-28 Create LICENSE
2025-01-28 okay, kicad-parse-gen doesn't work
2025-01-29 rename license so I can add apache and more tex
2025-01-29 Create APACHE-LICENSE
2025-01-31 lot of tex, might have gotten carried away
2025-01-31 split proposal to meet length requirement.
2025-02-02 fixing spelling (I can't spell algorithm)
2025-02-03 little readme update
2025-02-04 proposal update, citing and mvp
2025-02-05 this code is probably slow and bad
2025-02-05 add lcm code.
2025-02-05 some problems
2025-02-05 got it mostly working, besides need to figure placement area/board size
2025-02-05 update proposal to be more clear
2025-02-05 few more proposal updates
2025-02-06 got my chromosone sorted
2025-02-06 kind of getting to the point where a rewrite is needed
2025-02-07 refactoring (really bad)
2025-02-07 we can validate (this needs work)
2025-02-08 almost got swap working
2025-02-09 swap operator now works
2025-02-09 working on rotate
2025-02-10 rotation sort of working..
2025-02-10 fixed valid check
2025-02-10 make notebook
2025-02-11 commit b4 branch
2025-02-11 not working, too tired rn
2025-02-13 starting scoring
2025-02-15 last commit on this branch
2025-02-15 fixing it?
2025-02-15 working!
2025-02-15 fix array
2025-02-16 commit to save some progress b4 I break it
2025-02-16 done for the night I think
2025-02-16 we got it working the easy way
2025-02-16 current best is 10mil in 13s
2025-02-17 update for trying to clean up
2025-02-17 almost working !
2025-02-17 fixed bugs, now time to GA and add compaction operator
2025-02-17 figuring out comp
2025-02-17 ga working
2025-02-17 mostly working
2025-02-18 fix plotting
2025-02-18 it works!
2025-02-18 add pin and new rotate op
2025-02-18 add net coloring and refdes rename
2025-02-19 getting better
2025-02-19 quick commit for f64
2025-02-19 add better testing
2025-02-19 add gooder testing
2025-02-19 clippy fix
2025-02-20 test update
2025-02-22 add arduino and parsing code - shouldve updated sooner
2025-02-22 getting ready to switch to float bboxes
2025-02-24 getting close
2025-02-25 parsing is almost working :)
2025-02-25 need to figure out the bug with the pads
2025-02-25 commit for clippy fix
2025-02-25 clippied
2025-02-25 finally working but pins broken
2025-02-25 remove lock
2025-02-26 lots of changes, can recenter placement,etc
2025-02-26 trying update
2025-02-26 no warnings!
2025-02-28 GIF AND I AM MADE AN OBVIOUS MISTAKE
2025-02-28 new gif, probably should add this gitignore
2025-02-28 working so much better now
2025-02-28 update notebook
2025-02-28 added CLI using CLAP
2025-02-28 small changes but mightve broken it?
2025-02-28 little refactoring
2025-02-28 adding ability to plot scores
2025-02-28 fix score
2025-02-28 cleaning up, etc.
2025-02-28 updated gif
2025-02-28 moving folders
2025-03-02 add nets sort of
2025-03-04 breaking out code and starting rust doc
2025-03-05 switch to fp for selection
2025-03-06 some refactoring
2025-03-06 threads work but currently just for mutating pop
2025-03-06 committing before I try other thing
2025-03-10 small changes
2025-03-11 NEEDS A LOT OF WORKING BUT WORKING FASTER?? NEED TO TALK TO BART ABOUT RAND
2025-03-11 update notebook and change to only clone sometimes
2025-03-11 slower and worse??
2025-03-11 confirm double par is slower
2025-03-11 better?
2025-03-11 improving our selectors
2025-03-11 moved out the rand, think this makes it faster?
2025-03-11 adding comments for rust doc
2025-03-11 comments, going to clippy fix
2025-03-11 No errors. This will be my freeze for now. Going to mess with SA
2025-03-11 cleaning up my notebook
2025-03-12 start SA
2025-03-12 got SA working
2025-03-12 starting cleaning up the cli and better integrating the SA into this
2025-03-12 commit for clippy fixes
2025-03-12 cargo fmt + clippy
2025-03-13 adding PSA struct
2025-03-14 taking a break
2025-03-17 quick commit saving changes
2025-03-17 cleaning up clap mostly
2025-03-17 update readme and regen tests
2025-03-17 cleaning up
2025-03-17 cargo fmt
2025-03-17 cleaning up more
2025-05-01 add debugger, swap is causing overlaps.
2025-05-01 fixed overlap bug
2025-05-01 next update
2025-05-08 add good-er fixed
2025-05-08 can now take fixed from cli
2025-05-08 testing
2025-05-09 trying to place back to kicad

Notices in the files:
demo/layout1.kicad_pcb:
(c) 2015 productize
